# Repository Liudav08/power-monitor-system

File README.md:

# ESP32 Power Monitor System

A personal electronics project using an ESP32 and an INA219 sensor module to measure a DC load's voltage, current, and power, with a Python application for receiving measurements on a computer.

**Status:** Breadboard prototype working. The first PCB iteration is finished and a second iteration is being designed to replace the the microcontroller with ICs and the sensor module with a chip. 

## Why I built this

I wanted to design a measurement system that can connect embedded hardware to a computer while also working on my skills in sensor interfacing, firmware, python, and PCB design. 

A multimeter provides useful reference measurements, but this process focuses on automating the data colleciton. Its measurement accuracy still needs to be determined though through testing. 

## Project structure

| Path | Contents |
| --- | --- |
| [docs/setup.md](docs/setup.md) | Exact wiring and instructions for running the code |
| [docs/design.md](docs/design.md) | Component choices, calculations, and PCB decisions |
| [docs/build-log.md](docs/build-log.md) | Dated progress, problems, and fixes |
| [docs/images/](docs/images/) | Photos, diagrams, and PCB renders |
| [hardware/](hardware/) | Editable KiCad files |
| [firmware/](firmware/) | ESP32 code |
| [software/](software/) | Python code |
| [data/](data/) | Raw measurements |

## Project status

| Stage | Status |
| --- | --- |
| ESP32 and INA219 breadboard prototype | Working |
| Python serial reception | TODO: record current implementation status |
| Live plotting and CSV logging | planned |
| Measurement comparison with a multimeter | TODO: record completed tests |
| KiCad carrier PCB using existing modules | Completed |
| Later PCB with an INA219 IC and a custom microcontroller circuit | In development |

## How it works

The INA219 measures the voltage across its shunt resistor to determine current, and measures bus voltage at the load side. The ESP32 reads the sensor over I²C. The intended computer connection is USB serial, with Python receiving the measurements.

Section will be updated in the future as hardware is replaced with ICs and chips. 

## Hardware and software

| Item | Details |
| --- | --- |
| Microcontroller | ESP32 development board CP2102 |
| Sensor | INA219 breakout module - Generic INA219 w/ R100 shunt, 22 x 25mm |
| Test equipment | Variable DC power supply (0-10A, 0-30V) SPS30101N |
| Firmware | ESP32 firmware - Arduino IDE 2.3.10; libraries to be added |
| Computer application | Python 3.14 and VSCode 1.141 |
| PCB design | KiCad 10 and Altium designer 26.10.1 |

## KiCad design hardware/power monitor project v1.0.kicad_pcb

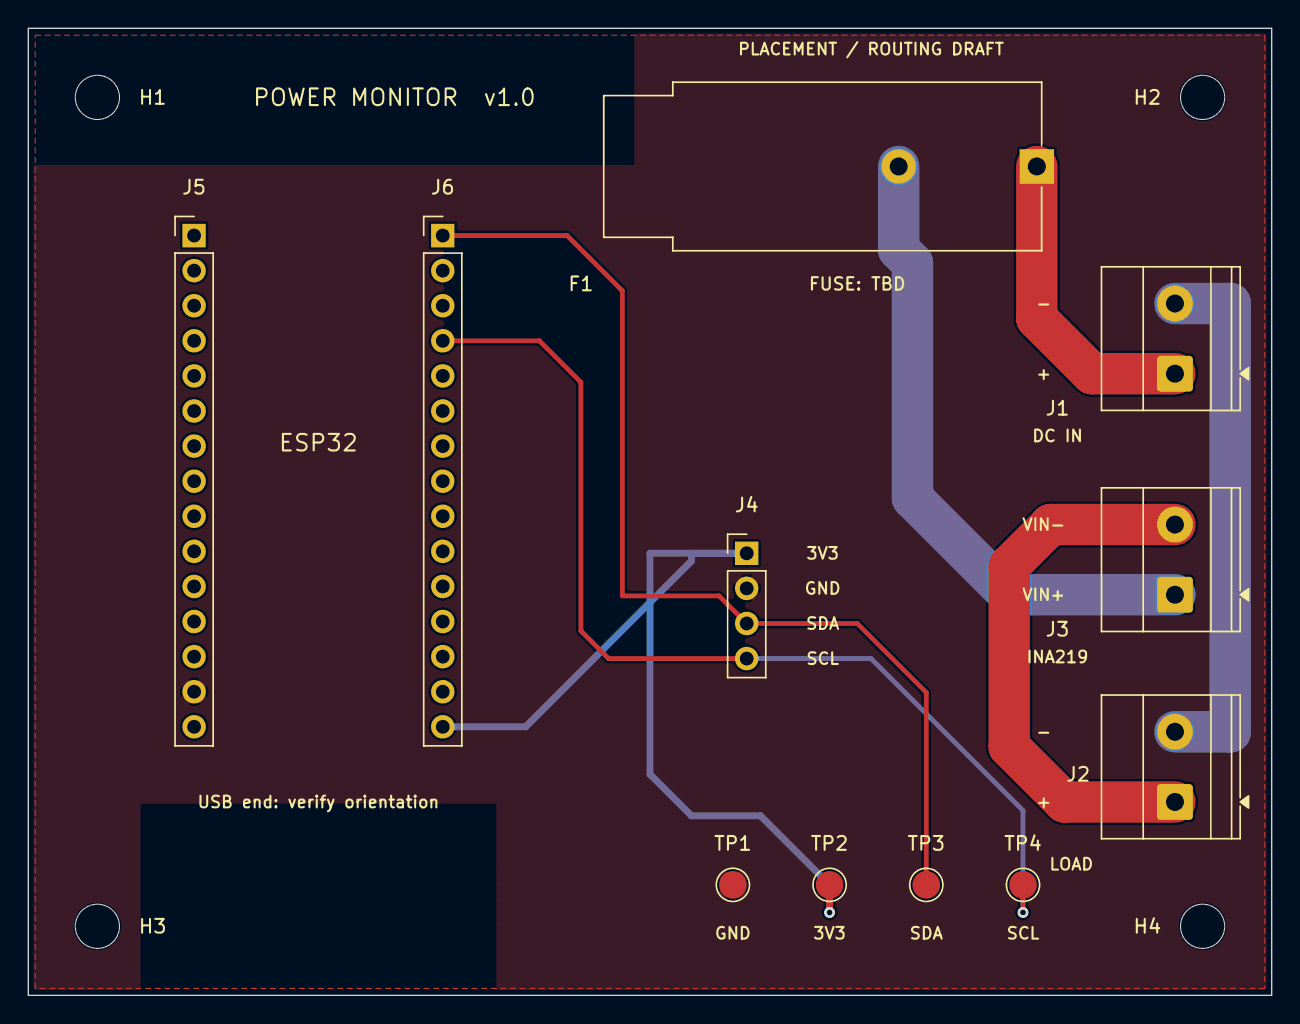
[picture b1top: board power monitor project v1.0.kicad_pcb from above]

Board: 2 copper layers, 90.0 x 70.0 mm, 15 parts (0 on the bottom side), 7 nets.

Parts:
F1: TBD; Fuseholder_Cylinder-5x20mm_Schurter_FAB_0031-355x_Horizonta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
H1, H2, H3, H4: M3; MountingHole_3.2mm_M3
J1: DC input; TerminalBlock_Phoenix_MKDS-1,5-2-5.08_1x02_P5.08mm_Horizont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
J2: Load output; TerminalBlock_Phoenix_MKDS-1,5-2-5.08_1x02_P5.08mm_Horizont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
J3: INA219 current terminals; TerminalBlock_Phoenix_MKDS-1,5-2-5.08_1x02_P5.08mm_Horizont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
J4: INA219 logic header; PinHeader_1x04_P2.54mm_Vertical
J5: ESP32 left header; PinHeader_1x15_P2.54mm_Vertical
J6: ESP32 right header; PinHeader_1x15_P2.54mm_Vertical
TP1: GND; TestPoint_Pad_D2.0mm
TP2: 3V3; TestPoint_Pad_D2.0mm
TP3: SDA; TestPoint_Pad_D2.0mm
TP4: SCL; TestPoint_Pad_D2.0mm

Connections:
+3V3: J4.1, J6.15, TP2.1 (1_1)
/I2C_SCL: J4.4, J6.4, TP4.1 (1_1)
/I2C_SDA: J4.3, J6.1, TP3.1 (1_1)
/SENSE_IN: F1.2, J3.1
/SENSE_OUT: J2.1, J3.2
/SUPPLY_POS: F1.1, J1.1
GND: J1.2, J2.2, J4.2, J5.14 (Pin_14_14), TP1.1 (1_1)

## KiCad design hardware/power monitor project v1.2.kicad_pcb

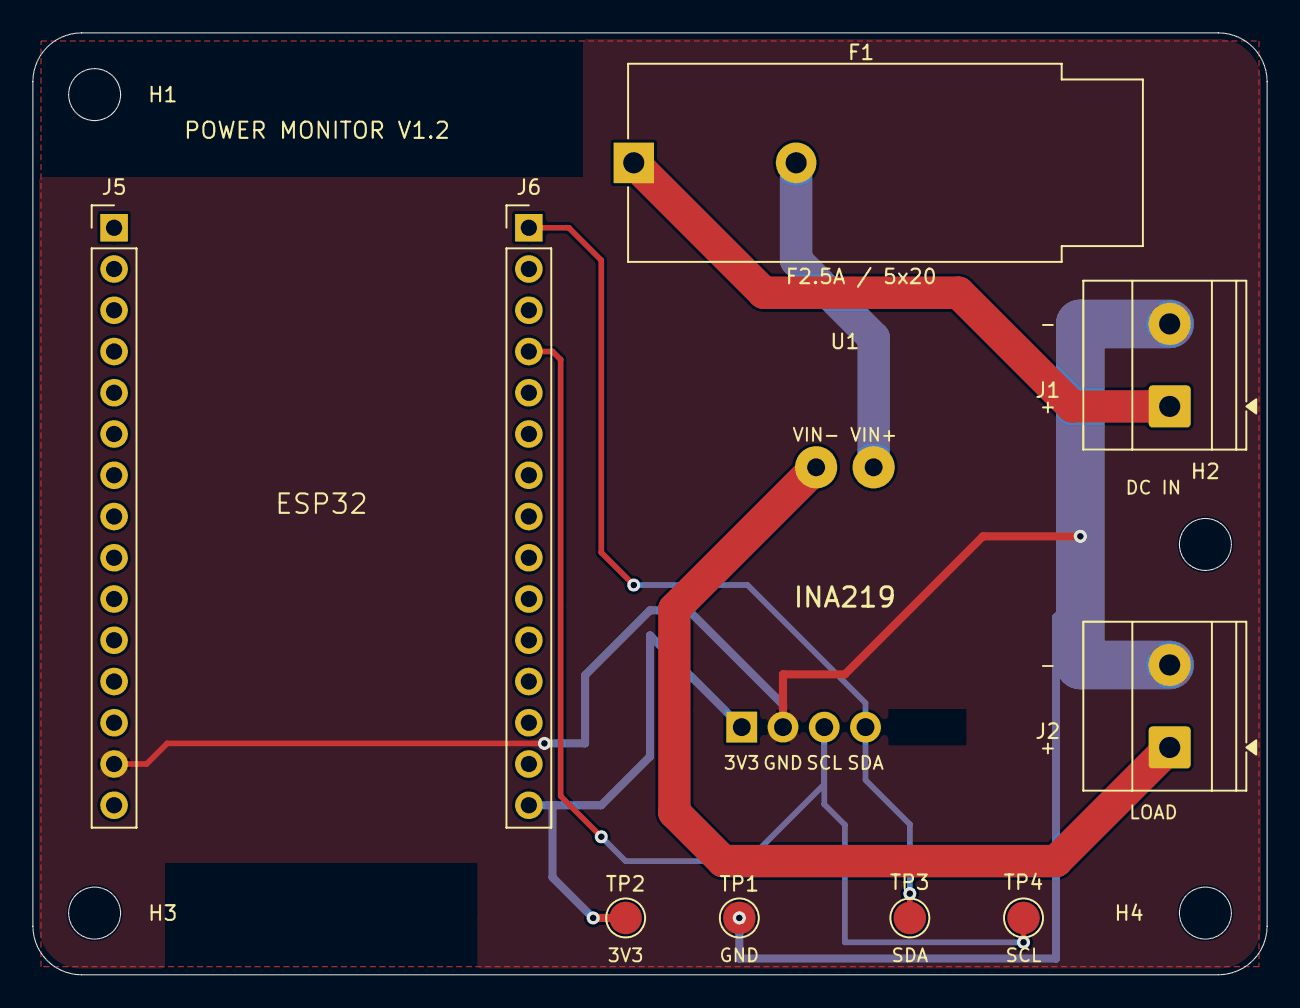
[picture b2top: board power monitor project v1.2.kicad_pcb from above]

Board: 2 copper layers, 76.0 x 58.0 mm, 14 parts (0 on the bottom side), 7 nets.

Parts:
F1: F2.5A; Fuseholder_Cylinder-5x20mm_Schurter_FAB_0031-355x_Horizonta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
H1, H2, H3, H4: M3; MountingHole_3.2mm_M3
J1: DC input; TerminalBlock_Phoenix_MKDS-1,5-2-5.08_1x02_P5.08mm_Horizont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
J2: Load output; TerminalBlock_Phoenix_MKDS-1,5-2-5.08_1x02_P5.08mm_Horizont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
J5: ESP32 left header; PinHeader_1x15_P2.54mm_Vertical
J6: ESP32 right header; PinHeader_1x15_P2.54mm_Vertical
TP1: GND; TestPoint_Pad_D2.0mm
TP2: 3V3; TestPoint_Pad_D2.0mm
TP3: SDA; TestPoint_Pad_D2.0mm
TP4: SCL; TestPoint_Pad_D2.0mm
U1: INA219_Module_DirectMount

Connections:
+3V3: J6.15, TP2.1 (1_1), U1.1
/I2C_SCL: J6.4, TP4.1 (1_1), U1.4
/I2C_SDA: J6.1, TP3.1 (1_1), U1.3
/SENSE_IN: F1.2, U1.5
/SENSE_OUT: J2.1, U1.6
/SUPPLY_POS: F1.1, J1.1
GND: J1.2, J2.2, J5.14 (Pin_14_14), TP1.1 (1_1), U1.2
